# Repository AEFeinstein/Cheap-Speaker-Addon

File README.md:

# Cheap-Speaker-Addon
Cheaper speaker addon for Magfest

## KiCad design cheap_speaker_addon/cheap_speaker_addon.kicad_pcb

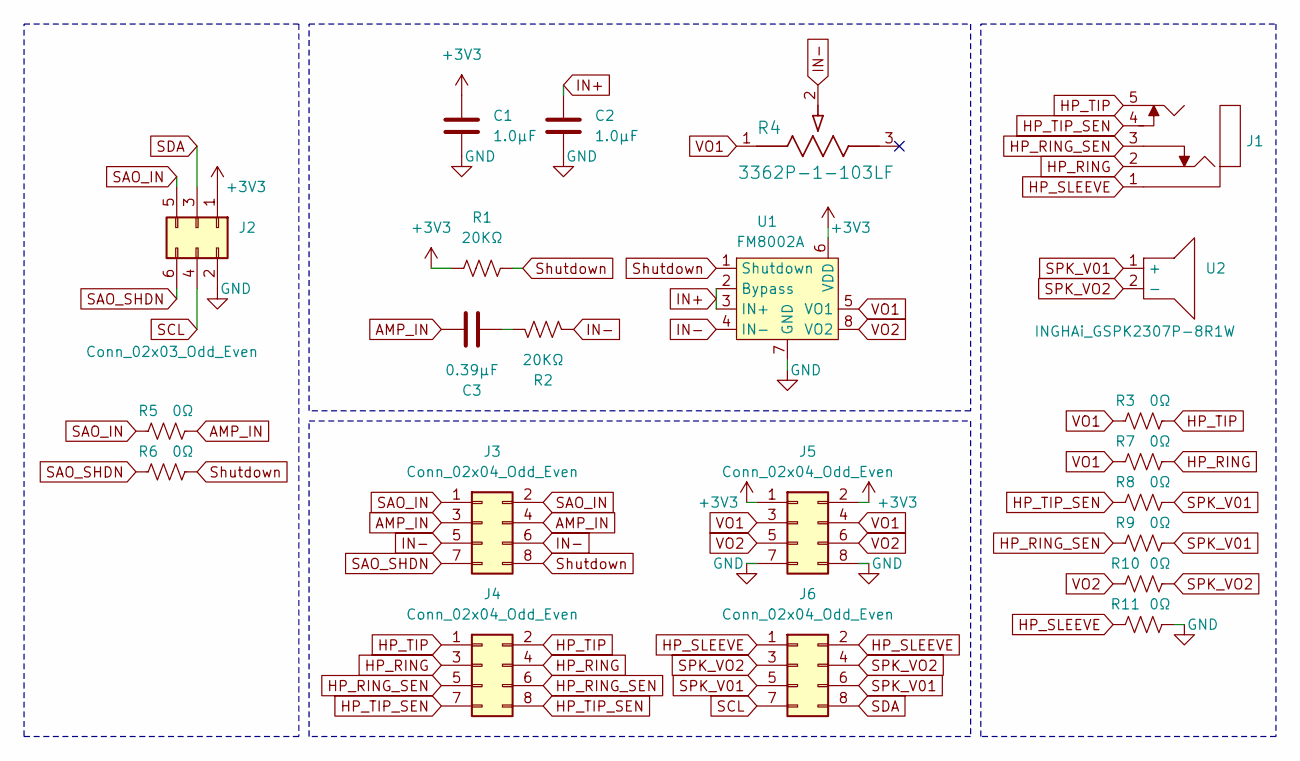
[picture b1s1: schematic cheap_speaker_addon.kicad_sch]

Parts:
C1, C2: 1.0µF; C_0603_1608Metric; LCSC C519560
C3: 0.39µF; C_0603_1608Metric; LCSC C376833
J1: PJ-307C; LCSC C16684
J2: Conn_02x03_Odd_Even; PinHeader_2x03_P2.54mm_Vertical; Digikey SFH11-PBPC-D03-ST-BK-ND
J3, J4, J5, J6: Conn_02x04_Odd_Even; PinHeader_2x04_P2.54mm_Vertical; LCSC C492421
R1, R2: 20KΩ; R_0603_1608Metric; LCSC C311888
R3, R5, R6, R7, R8, R9, R10, R11: 0Ω; R_0603_1608Metric; LCSC C2907080
R4: 3362P-1-103LF; POT_3362P; LCSC C118933
U1: FM8002A; SOP-8_3.9x4.9mm_P1.27mm; LCSC C94625
U2: INGHAi_GSPK2307P-8R1W; INGHAi GSPK2308P-8R0.5W; Digikey 102-2500-ND

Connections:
+3V3: C1.1, J2.1, J5.1, J5.2, R1.2, U1.6 (VDD)
AMP_IN: C3.1, J3.3, J3.4, R5.1
GND: C1.2, C2.2, J2.2, J5.7, J5.8, R11.1, U1.7 (GND)
HP_RING: J1.2, J4.3, J4.4, R7.1
HP_RING_SEN: J1.3, J4.5, J4.6, R9.2
HP_SLEEVE: J1.1, J6.1, J6.2, R11.2
HP_TIP: J1.5, J4.1, J4.2, R3.1
HP_TIP_SEN: J1.4, J4.7, J4.8, R8.2
IN+: C2.1, U1.2 (Bypass), U1.3 (IN+)
IN-: J3.5, J3.6, R2.2, R4.2, U1.4 (IN-)
unnamed: C3.2, R2.1
SAO_IN: J2.5, J3.1, J3.2, R5.2
SAO_SHDN: J2.6, J3.7, R6.2
SCL: J2.4, J6.7
SDA: J2.3, J6.8
SPK_V01: J6.5, J6.6, R8.1, R9.1, U2.1 (+)
SPK_VO2: J6.3, J6.4, R10.1, U2.2 (-)
Shutdown: J3.8, R1.1, R6.1, U1.1 (Shutdown)
VO1: J5.3, J5.4, R3.2, R4.1, R7.2, U1.5 (VO1)
VO2: J5.5, J5.6, R10.2, U1.8 (VO2)

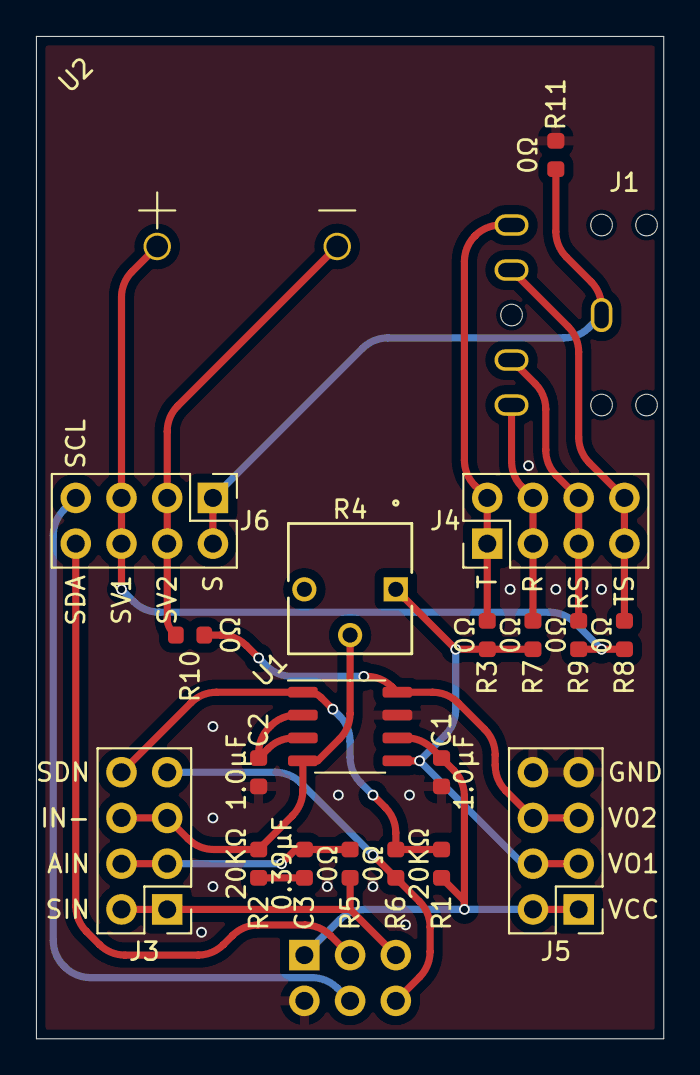
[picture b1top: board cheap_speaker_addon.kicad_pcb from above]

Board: 2 copper layers, 34.8 x 55.7 mm, 22 parts (1 on the bottom side), 20 nets.

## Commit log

2024-07-08 Add project
2024-07-08 Fix LCSC part numbers
